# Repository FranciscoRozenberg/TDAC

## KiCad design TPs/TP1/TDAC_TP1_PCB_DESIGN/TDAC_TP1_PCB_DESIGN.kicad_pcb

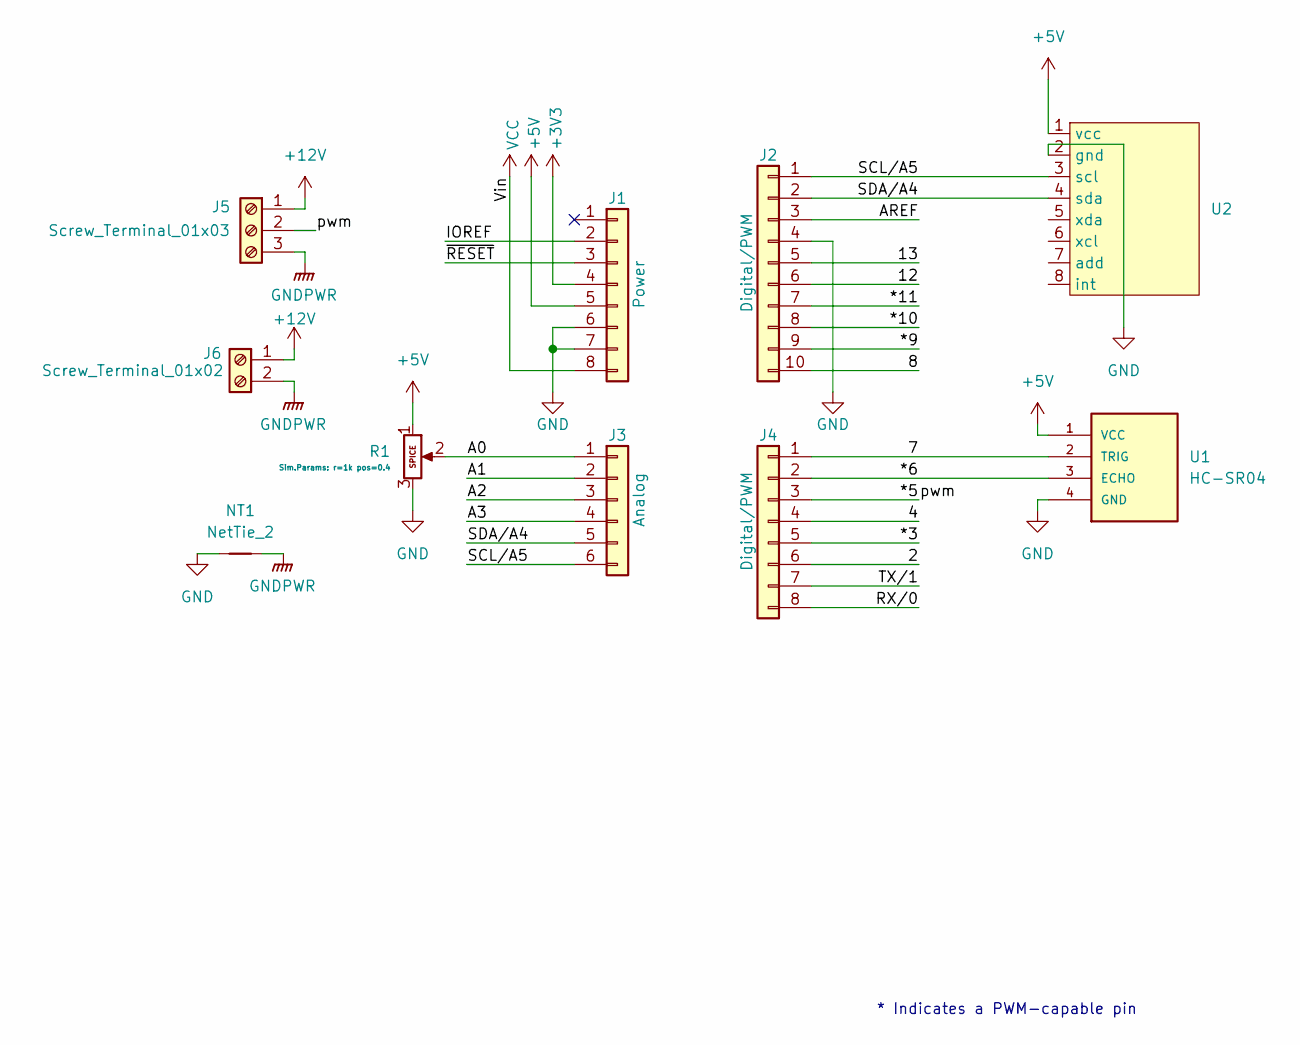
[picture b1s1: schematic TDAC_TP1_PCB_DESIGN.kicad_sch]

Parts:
J1: Power; PinSocket_1x08_P2.54mm_Vertical
J2: Digital/PWM; PinSocket_1x10_P2.54mm_Vertical
J3: Analog; PinSocket_1x06_P2.54mm_Vertical
J4: Digital/PWM; PinSocket_1x08_P2.54mm_Vertical
J5: Screw_Terminal_01x03; TerminalBlock_MaiXu_MX126-5.0-03P_1x03_P5.00mm
J6: Screw_Terminal_01x02; TerminalBlock_MaiXu_MX126-5.0-02P_1x02_P5.00mm
NT1: NetTie_2; NetTie-2_SMD_Pad2.0mm
R1: Potentiometer; Potentiometer_Alps_RK163_Single_Horizontal
U1: HC-SR04; XCVR_HC-SR04
U2: GY-521

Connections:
+3V3: J1.4
+5V: J1.5, R1.1, U1.1 (VCC), U2.1 (vcc)
+12V: J5.1, J6.1
/2: J4.6
/4: J4.4
/7: J4.1, U1.2 (TRIG)
/8: J2.10
/12: J2.6
/13: J2.5
/*3: J4.5
/*5: J4.3, J5.2
/*6: J4.2, U1.3 (ECHO)
/*9: J2.9
/*10: J2.8
/*11: J2.7
/A0: J3.1, R1.2
/A1: J3.2
/A2: J3.3
/A3: J3.4
/AREF: J2.3
/IOREF: J1.2
/RX/0: J4.8
/SCL/A5: J2.1, J3.6, U2.3 (scl)
/SDA/A4: J2.2, J3.5, U2.4 (sda)
/TX/1: J4.7
/~RESET: J1.3
GND: J1.6, J1.7, J2.4, NT1.1, R1.3, U1.4 (GND), U2.2 (gnd)
GNDPWR: J5.3, J6.2, NT1.2
VCC: J1.8

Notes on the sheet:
* Indicates a PWM-capable pin

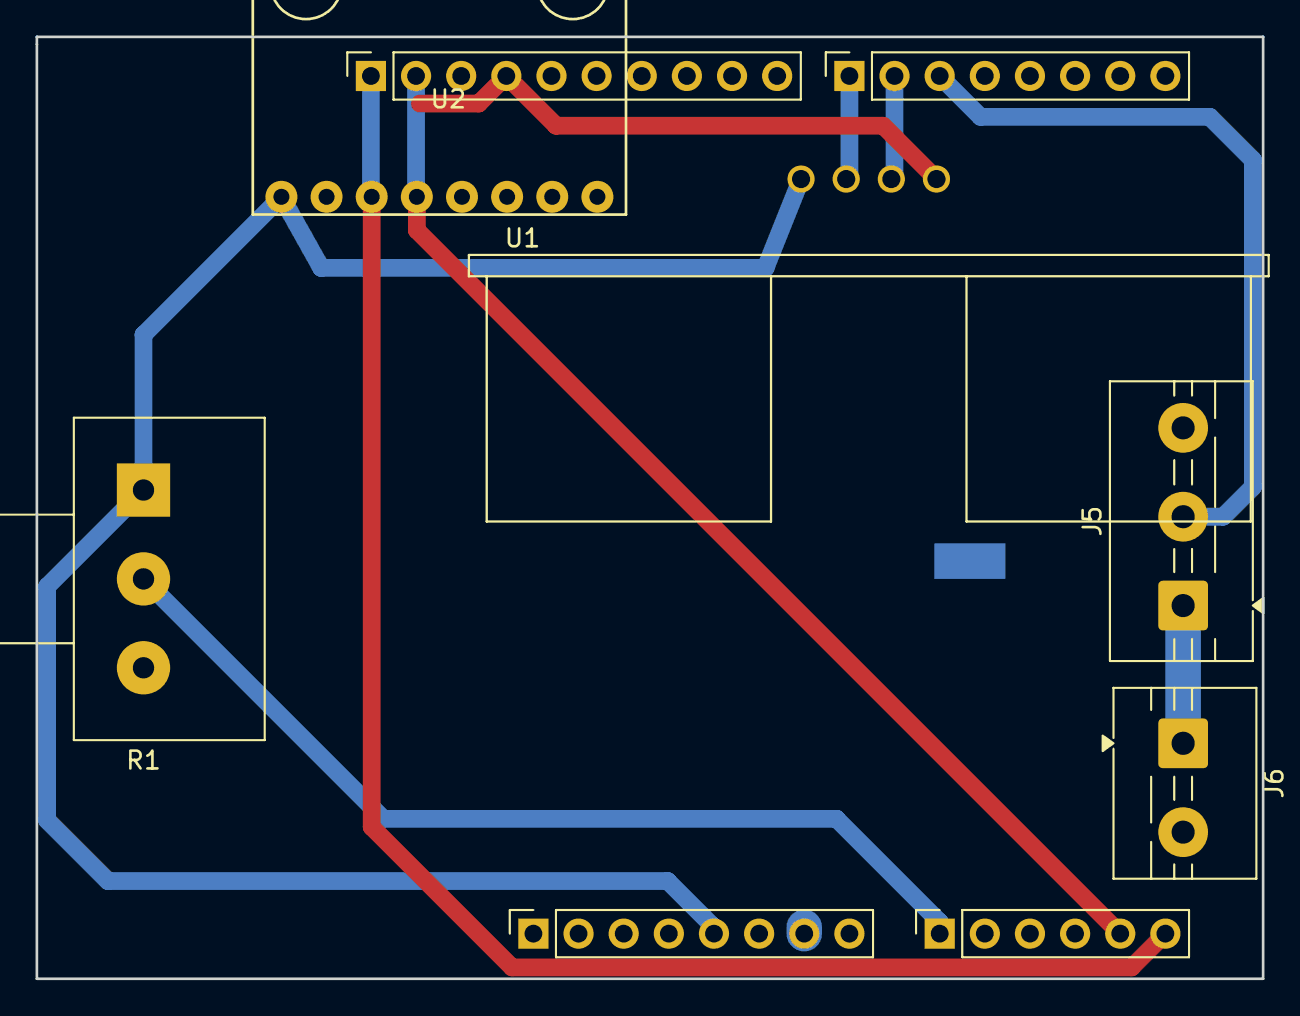
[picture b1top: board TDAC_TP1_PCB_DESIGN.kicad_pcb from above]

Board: 2 copper layers, 69.0 x 53.0 mm, 10 parts (1 on the bottom side), 10 nets.
